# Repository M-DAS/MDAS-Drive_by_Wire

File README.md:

# MDAS-Drive_by_Wire
The drive-by-wire division of the University of Michigan-Dearborn Autonomous Shuttle.

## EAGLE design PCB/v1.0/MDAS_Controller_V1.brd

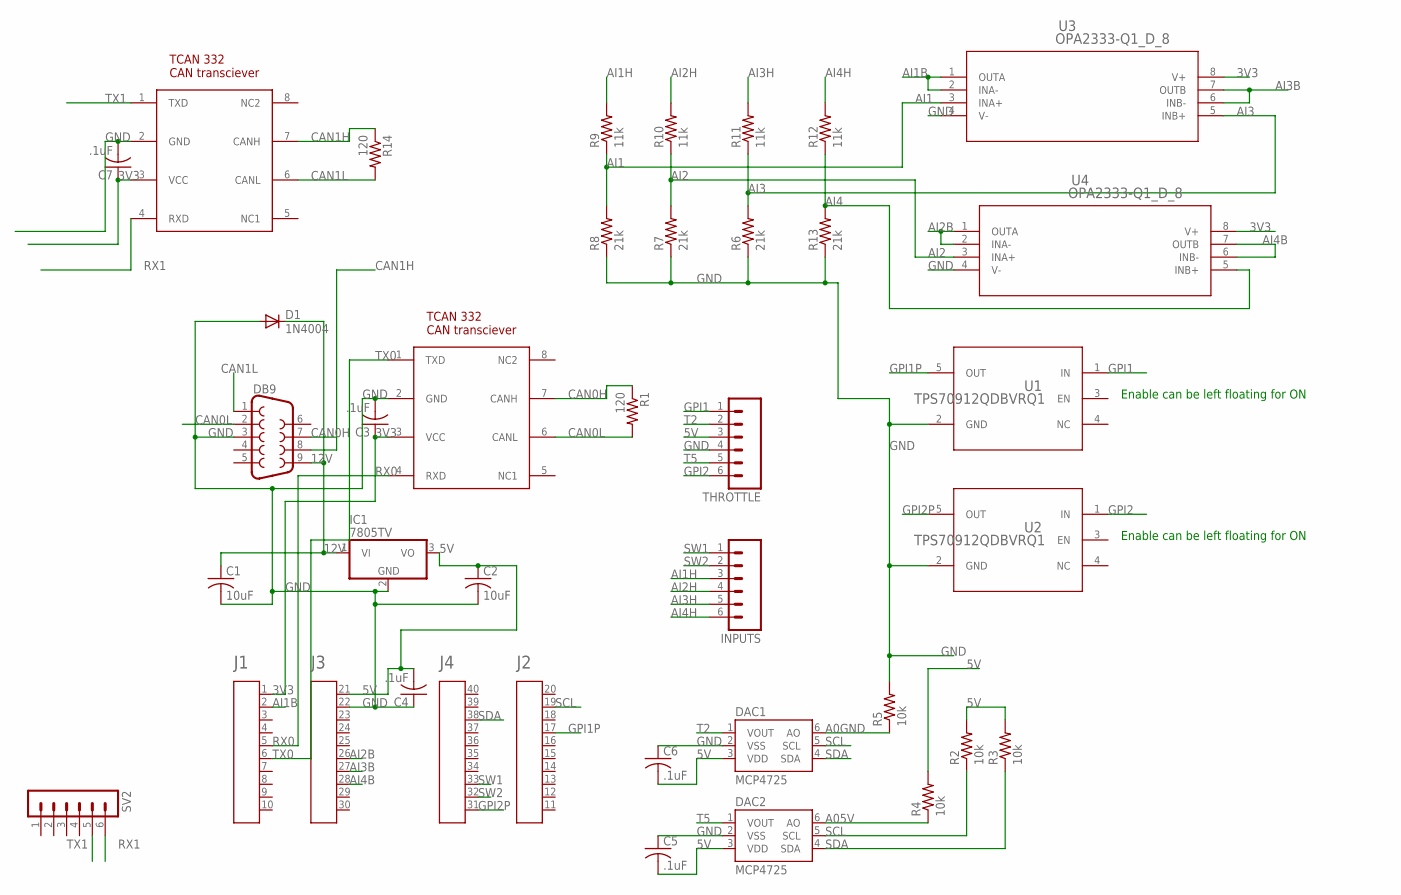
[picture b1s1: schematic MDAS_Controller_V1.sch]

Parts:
A1: HEADER4X10-BOOSTERPACK; 4X10-BOOSTERPACK
C1, C2: 10uF; C1206K
C3, C4, C5, C6, C7: .1uF; C0603
CAN_TRANSCIEVER, CAN_TRANSCIEVER1: TCAN332; SOIC127P600X172-8N
D1: 1N4004; DO41-10
DAC1, DAC2: MCP4725; SOT23-6
DB9: DB9FEMALE; DB9
IC1: 7805TV; TO220V
INPUTS: M06SMD-1MM; 1X06-1MM
R1, R14: 120; 0207/10
R2, R3, R4, R5: 10k; 0603-RES
R6, R7, R8, R13: 21k; R0603
R9, R10, R11, R12: 11k; R0603
SV2: MA06-1
THROTTLE: M06SMD-1MM; 1X06-1MM
U1, U2: TPS70912QDBVRQ1; DBV0005A_N
U3, U4: OPA2333-Q1_D_8; D8

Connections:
3V3: A1.1, C3.1, C7.1, CAN_TRANSCIEVER.3 (VCC), CAN_TRANSCIEVER1.3 (VCC), U3.8 (V+), U4.8 (V+)
5V: A1.21, C2.1, C4.2, C5.2, C6.2, DAC1.3 (VDD), DAC2.3 (VDD), IC1.3 (VO), R2.2, R3.2, R4.2, THROTTLE.3
12V: C1.1, D1.C, DB9.9, IC1.1 (VI)
A0GND: DAC1.6 (AO), R5.1
A05V: DAC2.6 (AO), R4.1
AI1: R8.2, R9.1, U3.3 (INA+)
AI1B: A1.2, U3.1 (OUTA), U3.2 (INA-)
AI1H: INPUTS.3, R9.2
AI2: R7.2, R10.1, U4.3 (INA+)
AI2B: A1.26, U4.1 (OUTA), U4.2 (INA-)
AI2H: INPUTS.4, R10.2
AI3: R6.2, R11.1, U3.5 (INB+)
AI3B: A1.27, U3.6 (INB-), U3.7 (OUTB)
AI3H: INPUTS.5, R11.2
AI4: R12.1, R13.2, U4.5 (INB+)
AI4B: A1.28, U4.6 (INB-), U4.7 (OUTB)
AI4H: INPUTS.6, R12.2
CAN0H: CAN_TRANSCIEVER.7 (CANH), DB9.7, R1.1
CAN0L: CAN_TRANSCIEVER.6 (CANL), DB9.2, R1.2
CAN1H: CAN_TRANSCIEVER1.7 (CANH), DB9.8, R14.1
CAN1L: CAN_TRANSCIEVER1.6 (CANL), DB9.1, R14.2
GND: A1.22, C1.2, C2.2, C3.2, C4.1, C5.1, C6.1, C7.2, CAN_TRANSCIEVER.2 (GND), CAN_TRANSCIEVER1.2 (GND), D1.A, DAC1.2 (VSS), DAC2.2 (VSS), DB9.3, IC1.2 (GND), R5.2, R6.1, R7.1, R8.1, R13.1, THROTTLE.4, U1.2 (GND), U2.2 (GND), U3.4 (V-), U4.4 (V-)
GPI1: THROTTLE.1, U1.1 (IN)
GPI1P: A1.17, U1.5 (OUT)
GPI2: THROTTLE.6, U2.1 (IN)
GPI2P: A1.31, U2.5 (OUT)
RX0: A1.5, CAN_TRANSCIEVER.4 (RXD)
RX1: CAN_TRANSCIEVER1.4 (RXD), SV2.6
SCL: A1.19, DAC1.5 (SCL), DAC2.5 (SCL), R2.1
SDA: A1.38, DAC1.4 (SDA), DAC2.4 (SDA), R3.1
SW1: A1.33, INPUTS.1
SW2: A1.32, INPUTS.2
T2: DAC1.1 (VOUT), THROTTLE.2
T5: DAC2.1 (VOUT), THROTTLE.5
TX0: A1.6, CAN_TRANSCIEVER.1 (TXD)
TX1: CAN_TRANSCIEVER1.1 (TXD), SV2.5

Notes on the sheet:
Enable can be left floating for ON

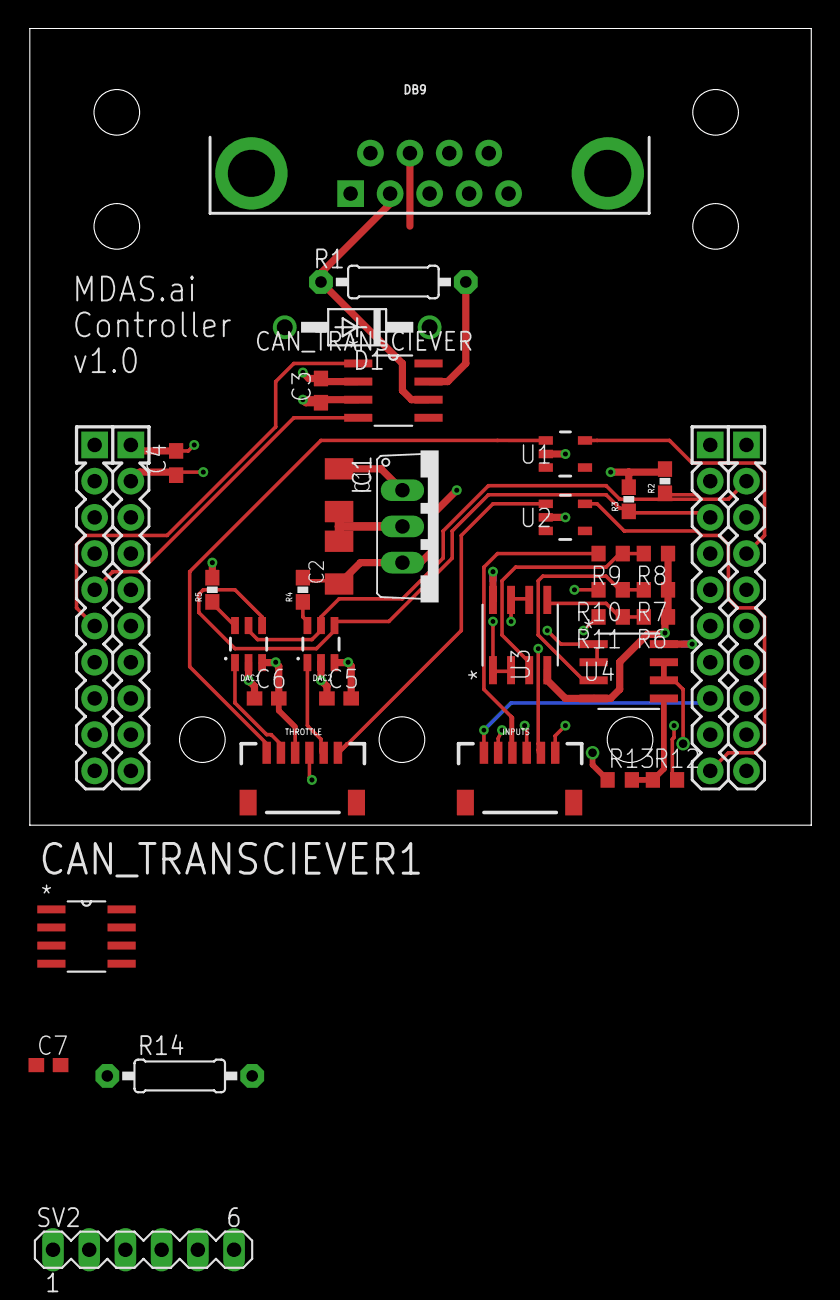
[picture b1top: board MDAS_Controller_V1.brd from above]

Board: 4 copper layers, 54.8 x 55.9 mm, 36 parts (0 on the bottom side), 36 nets.

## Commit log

2018-05-08 Create Hi
2018-05-08 Create pretend code
    code to annoy Ethan with
2018-05-08 Added Noah's files
2018-05-08 Folder or the braking actuator
2018-05-08 Steering Actuator files
2018-05-08 changed folder name
2018-05-25 test to annoy Ethan
2018-06-12 Changes to Steering Actuation
    Took the derivative between two torques and established a torque threshold based on the result. If the threshold was passed, it would change to a state that would keep the position of the wheels and 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
2018-07-09 My code after like 28 Days
    Steering stuff
2018-07-10 Added dac.c skeleton
    Missing scaling function. Will need scaling equation from throttle voltage range.
2018-07-10 Throttle Main Written
    Throttle Main has been written to the point that I only need the "write to DAC" functions and it''ll be good to be programmed.
2018-07-10 Fixed Typo
    Fixed typo << 1 vs << 2
2018-07-11 Changed Masking Logic
    Reversed logic from last iteration to only update data when the ID is found.
2018-07-23 Added DAC LUT
2018-07-23 Added dac.h
2018-07-23 Some throttle stuff
    The stuff I contributed to the main so that I can get Ben's baller helper function code.
2018-07-23 More throttle stuff
    I forgot to save it
2018-07-28 Finalized ADC, DAC functions
    ADC to percent still needs to be scaled to percent. Equation is currently missing. Drive_by_Wire.c will need to be updated to reflect DAC instead of digital potentiometers.
2018-07-30 Main Logic (7/29)
    Shouldn't include merge conflicts.
2018-07-30 Main Changes
    Minor Changes to Main since last commit.
2018-07-30 added v1.0 PCB files
2018-07-30 Fixed ADC input scaling
    Scaled ADC input to 0-100 percent
2018-07-31 Reupload Pedal_ADC.c
2018-07-31 Changes from 7-31-2018
    It compiled I promise.
2018-08-01 Reading over CAN
    Reads in messages over CAN and is now able to change states. As far as hardware goes, PCB has bad wire connection. Please remember to check.
2018-08-22 Current vehicle code
2018-08-22 PCB changes
2018-09-07 Add V2 Board to Repo
2018-09-23 Redesign routing
2018-09-26 Minor changes before Hughes manufactures

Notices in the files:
parts and their libraries:
SparkFun-Connectors: Licensing: Creative Commons ShareAlike 4.0 International - https://creativecommons.org/licenses/by-sa/4.0
